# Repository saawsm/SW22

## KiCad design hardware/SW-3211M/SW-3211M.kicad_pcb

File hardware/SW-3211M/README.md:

# SW-3211M, a MK-312 style driver on a stick!

## About
This board aims to bring the hardware of e-stim/EMS/TENS to an easy-to-use module. Think: Sparkfun, Adafruit, etc.

This device tries to mimic the output stage of the well-known Erostec ET312 or better, the DIY reverse engineered MK-312.
Hopefully by recreating this output stage, the same e-stim experience can be achieved as those devices.

Its been designed with the ESP-32 microcontroller in mind (hence SW-32), but should work with others. 

The original design of this module was based on the design by [WendyTeslaburger/WT-312](https://github.com/WendyTeslaburger/WT-312).

## Status
- [x] Create v1.0 Schematic
- [x] Route v1.0 PCB
- [x] Order v1.0 PCBs
- [ ] Review process
- [ ] Add alternative BOM sources

## Gerber & Bill of Materials (BOM)
The Gerber zip file was generated with JLCPCB in mind (excluding assembly).
Two BOM sources are available, the interactive HTML BOM located in `/bom` folder, or on [OctoPart](https://octopart.com/bom-tool/mcb9Iqj6).

## Theory of operation
### Output stage:

Just like the ET/MT312 this stick uses a 42TL004 audio transformer with the primary connected to the TENS output and the secondary connected to some circuitry to generate pulses.

These pulses are generated by the microcontroller, it can control frequency (how many pulses per second) and the duration of each pulse.

A single "pulse"  consists of two steps:
1. Apply a voltage on `PULSE_A`. This will make one of both N-FETs conductive and current will start to flow through half the windings of the transformer.
2. Apply a voltage on `PULSE_B`. This will make current flow through the other half of the transformer and reverse the polarity of the output TENS signal. Thus making this a bi-polar TENS driver.

To prevent the an excessive high drain-source voltage on the N-MOS drivers because of back-EMF generated by the transformer, two diodes will clamp this voltage to a zener diode on top of the centre-tap voltage.

### Level/current control

The intensity of a TENS stimulus is not only defined by the duration and frequency of the pulses, but also by the output power of that pulse. To control the output power of a pulse, we can limit how much current is flowing into the primary side of the transformer.

By controlling the gate-voltage of a P-FET it is possible to control how much current that P-FET will allow to flow. An opamp is used to boost the I/O-voltage of the microcontroller to the 9V needed on the P-FET gate.

Important to note is that the `I_LIMIT` signal is inverted, a 0V means the P-FET is allowing maximal current and a >3.3V will mean the P-FET is turned off.

### Current feedback

Because not all P-FETs are created 100% equally, it is important to first characterize the feedback curve between the `I_LIMIT` signal and the current flowing through the transformer. This curve can be measured by the MCU on a embedded or external ADC on the `I_SENSE` pin of the SW-3211M module.

To keep the voltage lost over the shunt resistor to a minimum, a small value shunt resistor is used and then amplified to the full-range of the ADC by an opamp.

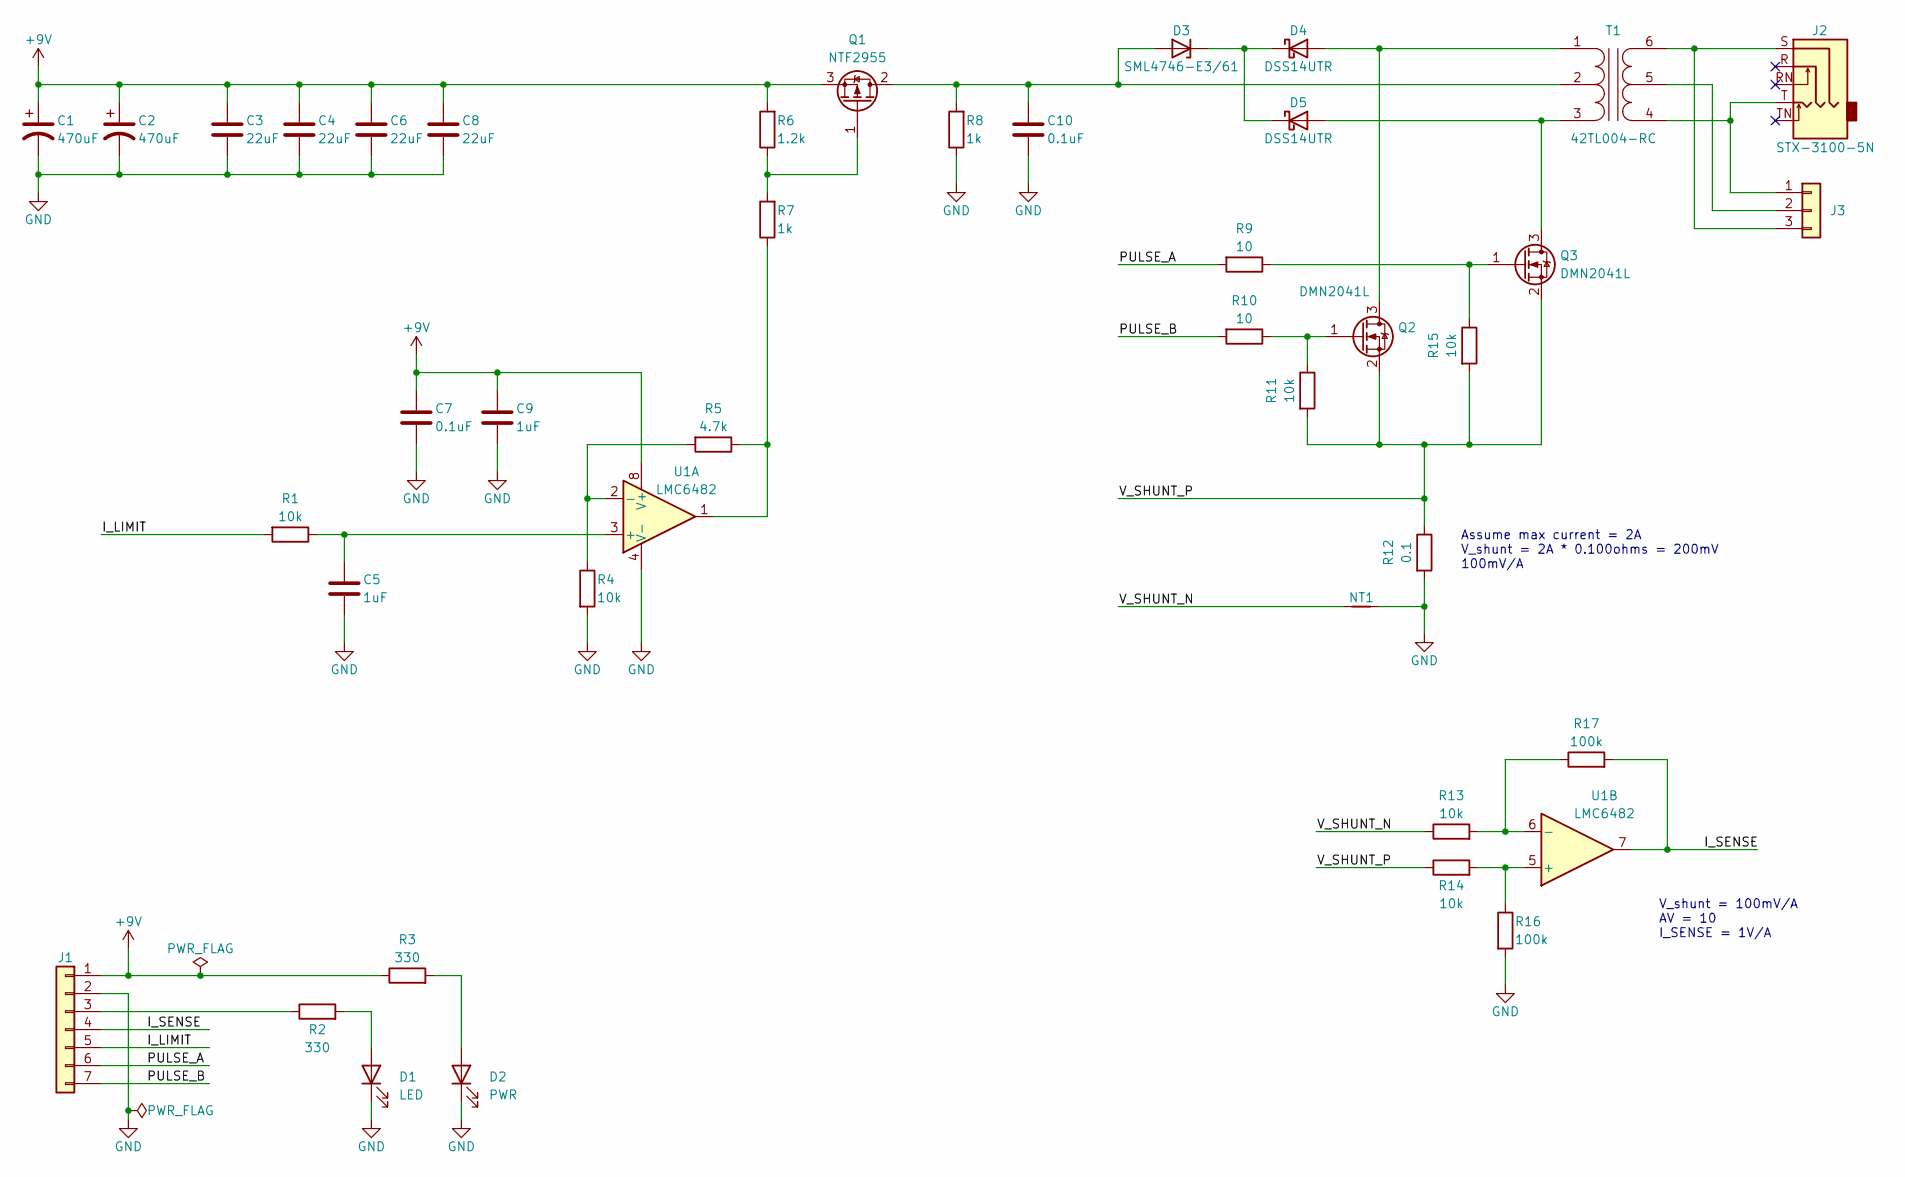
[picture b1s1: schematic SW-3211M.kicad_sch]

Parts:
C1, C2: 470uF; CP_Radial_D8.0mm_P3.50mm; MPN 477CKE016M
C3, C4, C6, C8: 22uF; C_1210_3225Metric; MPN CL32A226MAJNNNE
C5, C9: 1uF; C_0603_1608Metric; MPN CL10B105KA8NNNC
C7, C10: 0.1uF; C_0603_1608Metric; MPN CL10B104KB8WPND
D1: LED; LED_0805_2012Metric
D2: PWR; LED_0805_2012Metric
D3: SML4746-E3/61; D_SMA; MPN SML4746-E3/61
D4, D5: DSS14UTR; D_SOD-123F; MPN DSS14UTR
J1: Conn_01x07; PinHeader_1x07_P2.54mm_Vertical
J2: STX-3100-5N; MPN STX-3100-5N
J3: Conn_01x03; PinHeader_1x03_P2.54mm_Vertical
NT1: NetTie_2; NetTie-2_SMD_Pad0.5mm
Q1: NTF2955; SOT-223-3_TabPin2; MPN NTF2955T1G
Q2, Q3: DMN2041L; SOT-23; MPN DMN2041L-7
R1, R4, R11, R13, R14, R15: 10k; R_0603_1608Metric; MPN AC0603FR-1010KL
R2, R3: 330; R_0603_1608Metric
R5: 4.7k; R_0603_1608Metric; MPN AC0603FR-134K7L
R6: 1.2k; R_0603_1608Metric; MPN AC0603FR-071K2L
R7, R8: 1k; R_0603_1608Metric; MPN AC0603FR-101KL
R9, R10: 10; R_0603_1608Metric; MPN RC0603FR-0710RL
R12: 0.1; R_1206_3216Metric; MPN SCRR1206S1-R100F
R16, R17: 100k; R_0603_1608Metric; MPN CRCW0603100KFKEAC
T1: 42TL004-RC; 42TL; MPN 42TL004-RC
U1: LMC6482; SOIC-8_3.9x4.9mm_P1.27mm; MPN LMC6482IDT

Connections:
+9V: C1.1, C2.1, C3.1, C4.1, C6.1, C7.1, C8.1, C9.1, J1.1, Q1.3 (S), R3.1, R6.2, U1.8 (V+)
/I_LIMIT: J1.5, R1.2
/I_SENSE: J1.4, R17.2, U1.7
/PULSE_A: J1.6, R9.2
/PULSE_B: J1.7, R10.2
/V_SHUNT_N: NT1.1, R13.1
/V_SHUNT_P: Q2.2 (S), Q3.2 (S), R11.2, R12.1, R14.1, R15.2
GND: C1.2, C2.2, C3.2, C4.2, C5.2, C6.2, C7.2, C8.2, C9.2, C10.2, D1.1 (K), D2.1 (K), J1.2, NT1.2, R4.2, R8.1, R12.2, R16.2, U1.4 (V-)
unnamed: C5.1, R1.1, U1.3 (+)
unnamed: C10.1, D3.2 (A), Q1.2 (D), R8.2, T1.2 (PM)
unnamed: D1.2 (A), R2.2
unnamed: D2.2 (A), R3.2
unnamed: D3.1 (K), D4.1 (K), D5.1 (K)
unnamed: D4.2 (A), Q2.3 (D), T1.1 (PR1)
unnamed: D5.2 (A), Q3.3 (D), T1.3 (PR2)
unnamed: J1.3, R2.1
unnamed: J2.S, J3.3, T1.6 (S2)
unnamed: J2.T, J3.1, T1.4 (S1)
unnamed: J3.2, T1.5 (SM)
unnamed: Q1.1 (G), R6.1, R7.2
unnamed: Q2.1 (G), R10.1, R11.1
unnamed: Q3.1 (G), R9.1, R15.1
unnamed: R4.1, R5.2, U1.2 (-)
unnamed: R5.1, R7.1, U1.1
unnamed: R13.2, R17.1, U1.6 (-)
unnamed: R14.2, R16.1, U1.5 (+)

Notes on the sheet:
Assume max current = 2A V_shunt = 2A * 0.100ohms = 200mV 100mV/A
V_shunt = 100mV/A AV = 10 I_SENSE = 1V/A

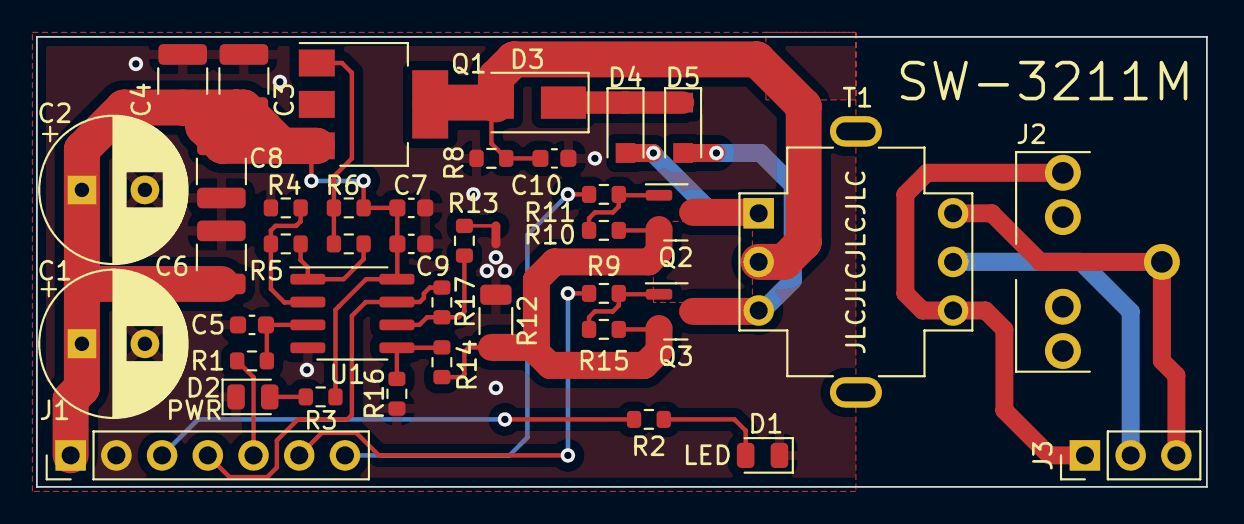
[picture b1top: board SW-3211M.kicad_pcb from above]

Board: 2 copper layers, 65.0 x 25.0 mm, 41 parts (0 on the bottom side), 26 nets.

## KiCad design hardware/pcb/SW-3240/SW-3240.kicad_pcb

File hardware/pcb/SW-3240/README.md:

# SW-3240 - Main Board

## About
This is a main board of SW-32. This specific board supports up to 4 output channels.
It provides power (+3.3V, +5V, and +9V), battery charging, and low-level control of the output modules.

## Status
- [x] Create v1.0 Schematic
- [x] Route v1.0 PCB
- [ ] Order v1.0 PCBs
- [ ] Review 

## Gerber & Bill of Materials (BOM)
The Gerber zip file was generated with JLCPCB in mind (excluding assembly).
Two BOM sources are available, the interactive HTML BOM located in `/bom` folder.

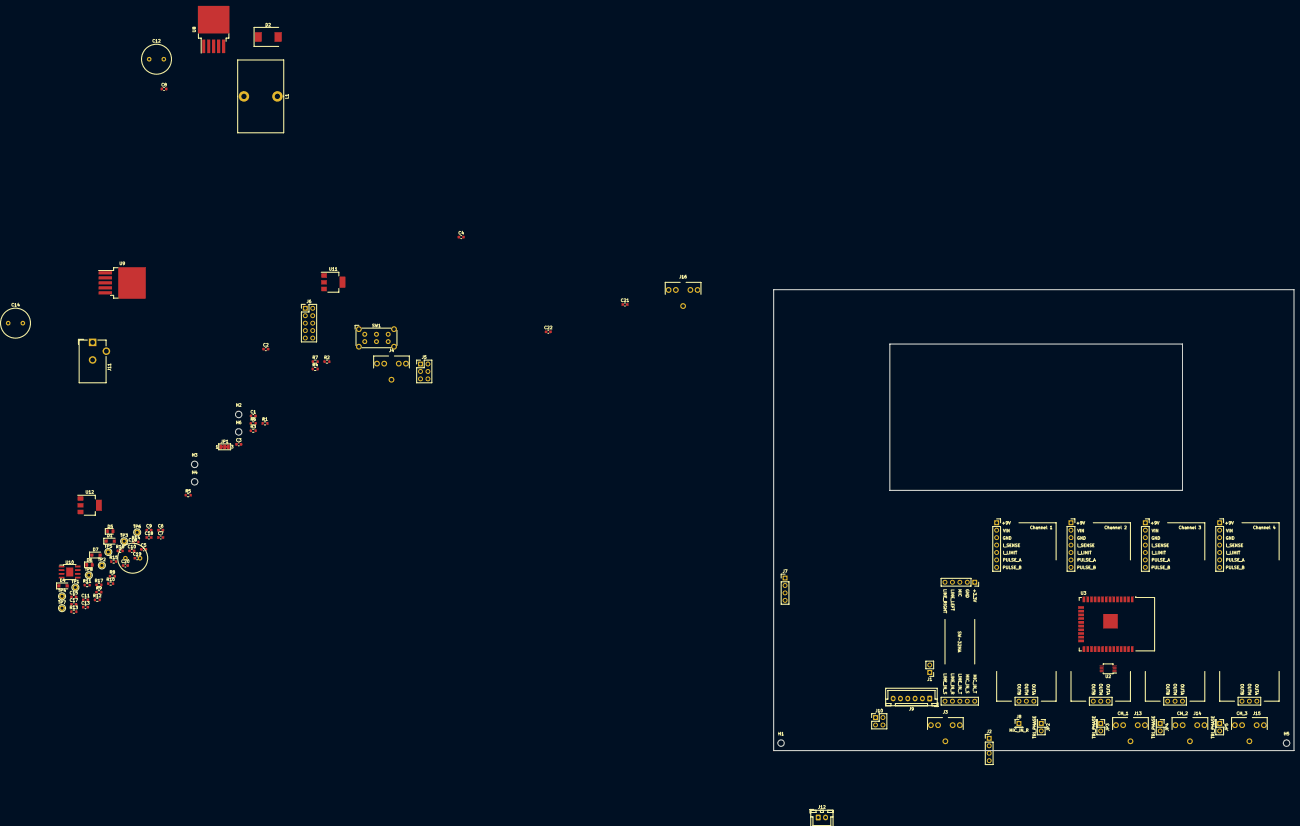
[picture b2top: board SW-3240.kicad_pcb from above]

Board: 2 copper layers, 177.8 x 157.5 mm, 94 parts (0 on the bottom side), 80 nets, no tracks yet.

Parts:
C1, C5, C7, C15, C17, C18, C19, C20: 10uF; C_0603_1608Metric
C2, C6, C13, C21, C22: 100nF; C_0603_1608Metric
C3, C8, C9: 100uF; C_0603_1608Metric
C4: 1uF; C_0603_1608Metric
C10: 470nF; C_0603_1608Metric
C11: 22nF; C_0603_1608Metric
C12, C14, C16: 1000uF; C_Radial_D10.0mm_H20.0mm_P5.00mm
D1, D4, D7: 1N4004; D_SOD-123F
D2: SS34; D_SMC
D5, D6: RED; LED_0805_2012Metric
H1, H2, H3, H4, H5, H6: MountingHole; MountingHole_2.2mm_M2
J1: AUX_MIC_IN; PinHeader_1x02_P2.54mm_Vertical
J2: AUX_LINE_IN; PinHeader_1x04_P2.54mm_Vertical
J3: MIC; STX-3100-5N
J4: LINE IN; STX-3100-5N
J5: ESPFlash; PinHeader_2x03_P2.54mm_Vertical
J6: JTAG; PinHeader_2x05_P2.54mm_Vertical
J7: I2C; PinHeader_1x04_P2.54mm_Vertical
J8: MIC_IN_R; PinHeader_1x01_P2.54mm_Vertical
J9: FP_IO; JST_XH_B6B-XH-A_1x06_P2.50mm_Vertical
J10: RESET/FLASH; PinHeader_2x02_P2.54mm_Vertical
J11: PWR; BarrelJack_CUI_PJ-102AH_Horizontal
J12: BAT; JST_XH_B2B-XH-A_1x02_P2.50mm_Vertical
J13: CH_1; STX-3100-5N
J14: CH_2; STX-3100-5N
J15: CH_3; STX-3100-5N
J16: CH_4; STX-3100-5N
JP1: SolderJumper_3_Bridged123; SolderJumper-3_P1.3mm_Bridged123_Pad1.0x1.5mm_NumberLabels
JP2, JP3, JP4, JP5: TRI_PHASE; PinHeader_2x01_P2.54mm_Vertical
L1: 100uH; L_Toroid_Vertical_L24.6mm_W15.5mm_P11.44mm_Pulse_KM-4
R1, R2, R6, R7, R17: 2.7K; R_0603_1608Metric
R3, R10, R16: 10K; R_0603_1608Metric
R4, R5: 10k; R_0603_1608Metric
R8, R12: 100K; R_0603_1608Metric
R9: 84.5K; R_0603_1608Metric
R11, R14: 1K; R_0603_1608Metric
R13: 9K; R_0603_1608Metric
R15: 470; R_0603_1608Metric
SW1: PWR_SW; SW_E-Switch_EG2219_DPDT_Angled
TP1: EN; TestPoint_THTPad_D2.0mm_Drill1.0mm
TP2: 5V; TestPoint_THTPad_D2.0mm_Drill1.0mm
TP3: 14V; TestPoint_THTPad_D2.0mm_Drill1.0mm
TP4: 9V; TestPoint_THTPad_D2.0mm_Drill1.0mm
TP5: 13.5V; TestPoint_THTPad_D2.0mm_Drill1.0mm
TP6: 12V; TestPoint_THTPad_D2.0mm_Drill1.0mm
TP7: 3.3V; TestPoint_THTPad_D2.0mm_Drill1.0mm
TP8: 3.3V_ALT; TestPoint_THTPad_D2.0mm_Drill1.0mm
U1: SW-32MA; SW-32MA_Socket
U2: MCP4728; MSOP-10_3x3mm_P0.5mm
U3: ESP32-WROOM-32D; ESP32-WROOM-32
U4: Channel 1; SW-32MO_Socket
U5: Channel 2; SW-32MO_Socket
U6: Channel 3; SW-32MO_Socket
U7: Channel 4; SW-32MO_Socket
U8: LM2576-5; TO-263-5_TabPin3
U9: LM2941; TO-263-5_TabPin3
U10: LMR14050; TI_SO-PowerPAD-8
U11, U12: NCP1117-3.3; SOT-223-3_TabPin2

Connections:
+3V3: C1.1, C2.1, C3.1, C5.1, C6.1, C19.1, C21.1, J5.2, J6.1, J7.2, JP1.2 (C), R1.1, R2.1, R4.2, R5.2, R15.2, TP7.1, U1.1 (+3.3V), U2.1 (VDD), U3.2 (VDD), U4.2 (VIN), U5.2 (VIN), U6.2 (VIN), U7.2 (VIN), U11.2 (VO)
+5V: C12.1, C15.1, C17.1, C18.1, L1.2, TP2.1, U8.4 (FB), U11.3 (VI), U12.3 (VI)
+9V: R12.1, R14.2, TP4.1, U4.1 (+9V), U5.1 (+9V), U6.1 (+9V), U7.1 (+9V)
+12V: C7.1, C8.1, C9.1, R16.1, SW1.2 (B), TP6.1, U8.1 (VIN), U10.2 (VIN)
/+3.3V_FP: C20.1, C22.1, J9.2, TP8.1, U12.2 (VO)
/CHA_I_LIMIT: U2.6 (VOUTA), U4.5 (I_LIMIT)
/CHA_I_SENSE: U3.7 (IO35), U4.4 (I_SENSE)
/CHA_PULSE_A: U3.26 (IO4), U4.6 (PULSE_A)
/CHA_PULSE_B: U3.24 (IO2), U4.7 (PULSE_B)
/CHB_I_LIMIT: U2.7 (VOUTB), U5.5 (I_LIMIT)
/CHB_I_SENSE: U3.6 (IO34), U5.4 (I_SENSE)
/CHB_PULSE_A: U3.31 (IO19), U5.6 (PULSE_A)
/CHB_PULSE_B: U3.30 (IO18), U5.7 (PULSE_B)
/CHC_I_LIMIT: U2.8 (VOUTC), U6.5 (I_LIMIT)
/CHC_I_SENSE: U3.5 (SENSOR_VN), U6.4 (I_SENSE)
/CHC_PULSE_A: U3.37 (IO23), U6.6 (PULSE_A)
/CHC_PULSE_B: U3.9 (IO33), U6.7 (PULSE_B)
/CHD_I_LIMIT: U2.9 (VOUTD), U7.5 (I_LIMIT)
/CHD_I_SENSE: U3.4 (SENSOR_VP), U7.4 (I_SENSE)
/CHD_PULSE_A: U3.28 (IO17), U7.6 (PULSE_A)
/CHD_PULSE_B: U3.27 (IO16), U7.7 (PULSE_B)
/CH_PSU_EN: J9.5, R8.1, TP1.1, U10.3 (EN)
/DAC_SCL: R1.2, U2.2 (SCL), U3.29 (IO5)
/DAC_SDA: R2.2, U2.3 (SDA), U3.8 (IO32)
/EN: C4.1, J5.1, J10.2, R5.1, U3.3 (EN)
/IO0: J5.6, J10.4, R4.1, U3.25 (IO0)
/LINE_LEFT: U1.4 (LINE_LEFT), U3.11 (IO26)
/LINE_RIGHT: U1.5 (LINE_RIGHT), U3.10 (IO25)
/MIC: U1.3 (MIC), U3.12 (IO27)
/MTCK: J6.4, U3.16 (IO13)
/MTDI: J6.8, U3.14 (IO12)
/MTDO: J6.6, U3.23 (IO15)
/MTMS: J6.2, U3.13 (IO14)
/PSU/VIN: D1.2 (A), J11.1
/RXD: J5.5, U3.34 (RXD0/IO3)
/SCL: J7.3, J9.3, R6.2, U3.36 (IO22)
/SDA: J7.4, J9.4, R7.2, U3.33 (IO21)
/TXD: J5.3, U3.35 (TXD0/IO1)
/VBAT_SENSE: J9.6, R16.2, R17.1
GND: C1.2, C2.2, C3.2, C4.2, C5.2, C6.2, C7.2, C8.2, C9.2, C10.2, C11.1, C12.2, C14.2, C15.2, C16.2, C17.2, C18.2, C19.2, C20.2, C21.2, C22.2, D2.2 (A), D5.1 (K), D6.1 (K), D7.2 (A), J5.4, J6.3, J7.1, J9.1, J10.1, J10.3, J11.2, J12.2, R3.1, R8.2, R9.2, R11.2, R13.2, R17.2, U1.2 (GND), U2.10 (VSS), U3.1 (GND), U3.15 (GND), U3.38 (GND), U3.39 (GND), U4.3 (GND), U5.3 (GND), U6.3 (GND), U7.3 (GND), U8.3 (GND), U8.5 (~ON/OFF), U9.2 (ON/OFF), U9.3 (GND), U10.7 (GND), U10.9 (GNDPAD), U11.1 (GND), U12.1 (GND)
unnamed: C10.1, D1.1 (K), U9.4 (IN)
unnamed: C11.2, U10.6 (SS)
unnamed: C13.1, U10.1 (BOOT)
unnamed: C13.2, U10.8 (SW)
unnamed: C14.1, D4.2 (A), R10.1, TP3.1, U9.5 (OUT)
unnamed: C16.1, D7.1 (K), SW1.1 (A), TP5.1
unnamed: D2.1 (K), L1.1, U8.2 (OUT)
unnamed: D5.2 (A), R14.1
unnamed: D6.2 (A), R15.1
unnamed: J1.1, J3.S, U1.7 (MIC_IN_S)
unnamed: J1.2, J3.TN
unnamed: J2.1, J4.TN
unnamed: J2.2, J2.3, J4.S, U1.10 (LINE_IN_S)
unnamed: J2.4, J4.RN
unnamed: J3.R, J8.1
unnamed: J3.T, U1.6 (MIC_IN_T)
unnamed: J4.R, U1.9 (LINE_IN_R)
unnamed: J4.T, U1.8 (LINE_IN_T)
unnamed: J13.R, JP2.2 (B)
unnamed: J13.S, U4.8 (OUTA)
unnamed: J13.T, U4.10 (OUTB)
unnamed: J14.R, JP3.2 (B)
unnamed: J14.S, U5.8 (OUTA)
unnamed: J14.T, U5.10 (OUTB)
unnamed: J15.R, JP4.2 (B)
unnamed: J15.S, U6.8 (OUTA)
unnamed: J15.T, U6.10 (OUTB)
unnamed: J16.R, JP5.2 (B)
unnamed: J16.S, U7.8 (OUTA)
unnamed: J16.T, U7.10 (OUTB)
unnamed: JP1.1 (A), R7.1
unnamed: JP1.3 (B), R6.1
unnamed: JP2.1 (A), U4.9 (OUTM)
unnamed: JP3.1 (A), U5.9 (OUTM)
unnamed: JP4.1 (A), U6.9 (OUTM)
unnamed: JP5.1 (A), U7.9 (OUTM)
unnamed: R3.2, U2.4 (~LDAC)
unnamed: R9.1, U10.4 (RT/SYNC)
unnamed: R10.2, R11.1, U9.1 (ADJ)
unnamed: R12.2, R13.1, U10.5 (FB)

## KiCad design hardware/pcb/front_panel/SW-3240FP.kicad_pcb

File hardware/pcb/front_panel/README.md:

# SW-324FP - Front Panel

## About
This is the front panel board for the SW-324. It connects via the I2C expansion connector on the main board.

## Status
- [x] Create v1.1 Schematic
- [ ] Route v1.1 PCB
- [ ] Order v1.1 PCBs
- [ ] Review

## Gerber & Bill of Materials (BOM)
The Gerber zip file was generated with [JLCPCB](https://jlcpcb.com/) in mind (excluding assembly).
Two BOM sources are available, the interactive HTML BOM located in `/bom` folder, and a CSV file.

### Excluded BOM Items:
- 0.1" break-away pin headers/sockets
- Misc connectors

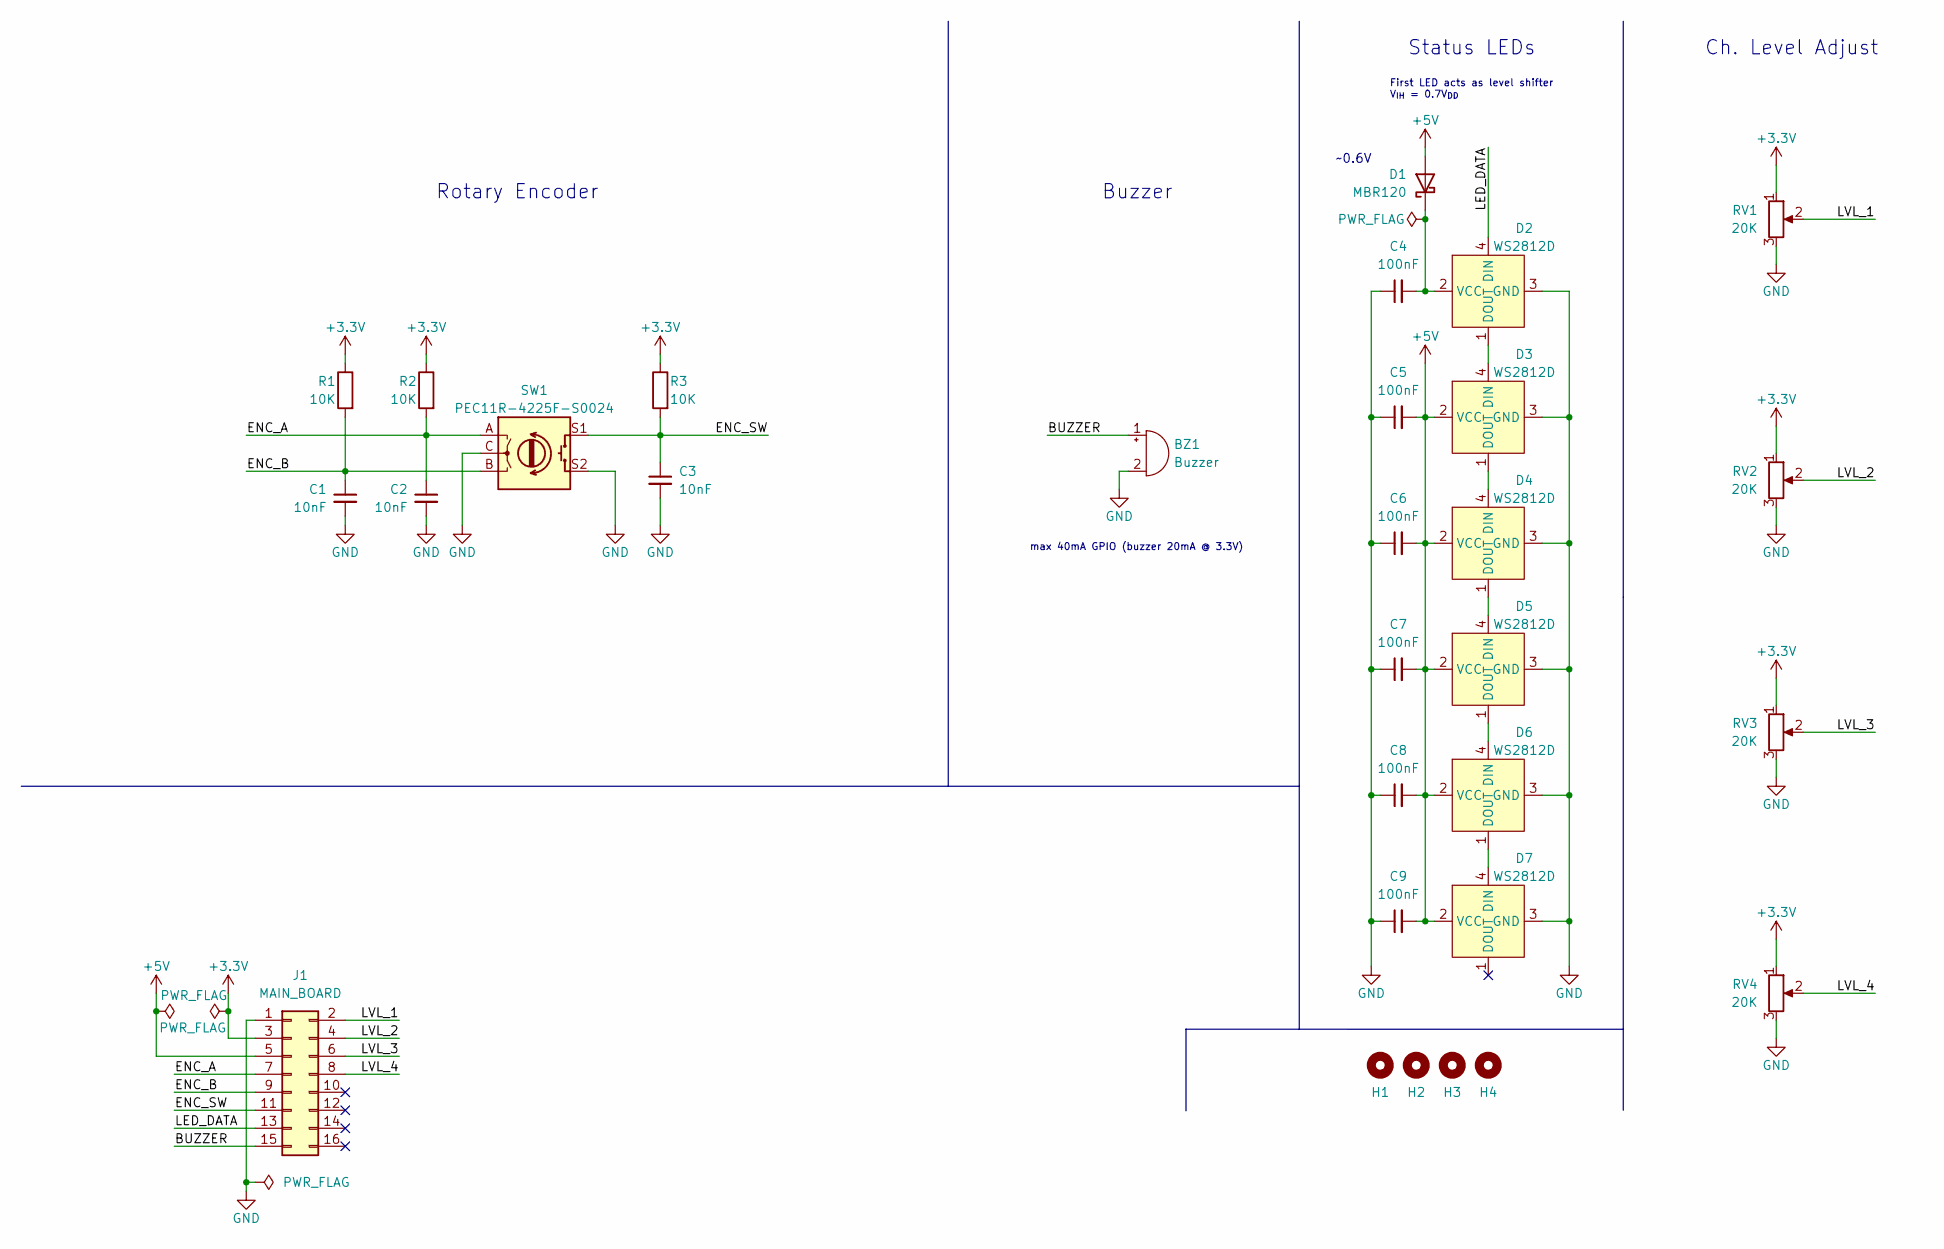
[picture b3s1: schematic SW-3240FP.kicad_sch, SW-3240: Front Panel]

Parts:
BZ1: Buzzer; Buzzer_12x9.5RM7.6; MPN IE122303-1; MOUSER 497-IE122303-1
C1, C2, C3: 10nF; C_0603_1608Metric; MPN CL10B103KB8NNNC; LCSC C1589
C4, C5, C6, C7, C8, C9: 100nF; C_0603_1608Metric; MPN CL10B104KB8NNNC; LCSC C1591
D1: MBR120; D_SOD-123F; MPN MBR120ESFT1G; MOUSER 863-MBR120ESFT1G
D2, D3, D4, D5, D6, D7: WS2812D; WS2812D-F5; MPN WS2812D-F5; LCSC C190565
H1, H2, H3, H4: MountingHole; MountingHole_2.2mm_M2
J1: MAIN_BOARD; PinHeader_2x08_P2.54mm_Vertical
R1, R2, R3: 10K; R_0603_1608Metric; MPN RC0603FR-0710KL; LCSC C98220
RV1, RV2, RV3, RV4: 20K; Potentiometer_Bourns_PTV09A-1_Single_Vertical; MPN PTV09A-40xxS-A203
SW1: PEC11R-4225F-S0024; Rotary_Encoder_Switched_PEC11R; MPN PEC11R-42xxK-S0024

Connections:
+3V3: J1.3, R1.1, R2.1, R3.1, RV1.1, RV2.1, RV3.1, RV4.1
+5V: C5.2, C6.2, C7.2, C8.2, C9.2, D1.2 (A), D3.2 (VCC), D4.2 (VCC), D5.2 (VCC), D6.2 (VCC), D7.2 (VCC), J1.5
/BUZZER: BZ1.1 (-), J1.15
/ENC_A: C2.1, J1.7, R2.2, SW1.A
/ENC_B: C1.1, J1.9, R1.2, SW1.B
/ENC_SW: C3.1, J1.11, R3.2, SW1.S1
/LED_DATA: D2.4 (DIN), J1.13
/LVL_1: J1.2, RV1.2
/LVL_2: J1.4, RV2.2
/LVL_3: J1.6, RV3.2
/LVL_4: J1.8, RV4.2
GND: BZ1.2 (+), C1.2, C2.2, C3.2, C4.1, C5.1, C6.1, C7.1, C8.1, C9.1, D2.3 (GND), D3.3 (GND), D4.3 (GND), D5.3 (GND), D6.3 (GND), D7.3 (GND), J1.1, RV1.3, RV2.3, RV3.3, RV4.3, SW1.C, SW1.S2
unnamed: C4.2, D1.1 (K), D2.2 (VCC)
unnamed: D2.1 (DOUT), D3.4 (DIN)
unnamed: D3.1 (DOUT), D4.4 (DIN)
unnamed: D4.1 (DOUT), D5.4 (DIN)
unnamed: D5.1 (DOUT), D6.4 (DIN)
unnamed: D6.1 (DOUT), D7.4 (DIN)

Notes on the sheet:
Status LEDs
~0.6V
Rotary Encoder
Ch. Level Adjust
Buzzer
First LED acts as level shifter V_{IH} = 0.7V_{DD}
max 40mA GPIO (buzzer 20mA @ 3.3V)

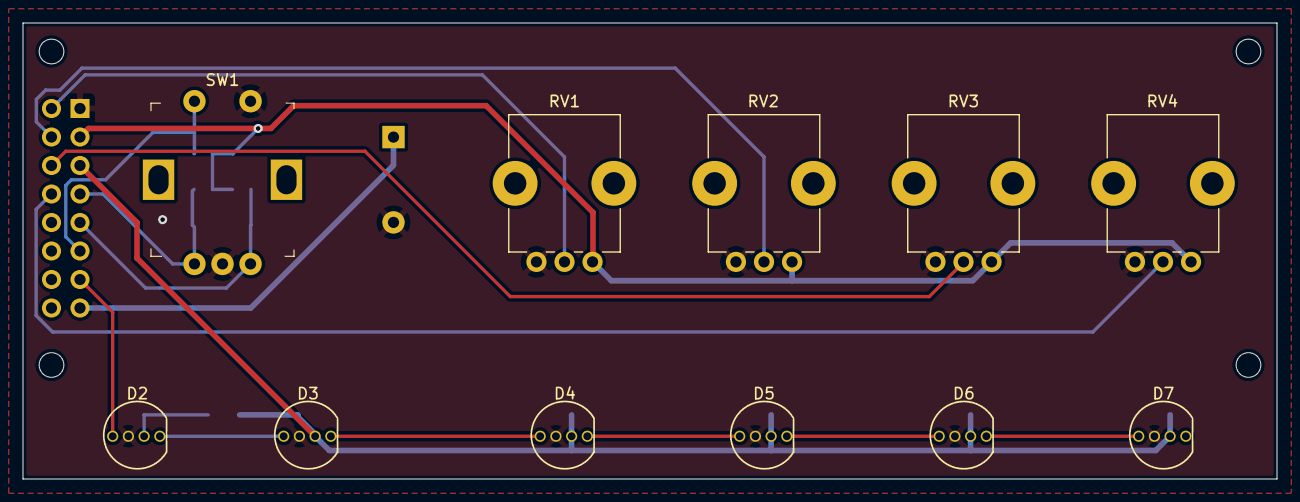
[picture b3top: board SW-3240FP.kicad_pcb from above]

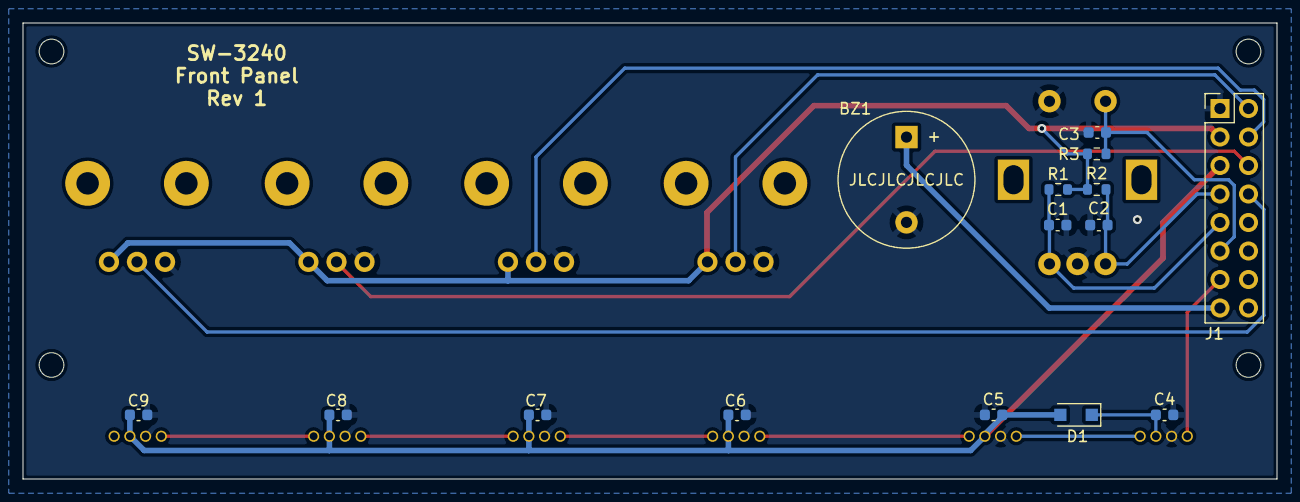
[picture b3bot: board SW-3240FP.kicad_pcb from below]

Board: 2 copper layers, 111.8 x 40.6 mm, 30 parts (19 on the bottom side), 18 nets.

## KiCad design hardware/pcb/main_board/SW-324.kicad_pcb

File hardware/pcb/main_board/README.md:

# SW-324 - Main Board

## About
This is a main board of SW-324. It supports a max of four output (stim) channels, and two AUX channels.
It provides power (+3.3V, +5V, and +9V), battery charging, low-level control of the output modules (via a Raspberry Pi Pico), and high-level control via an ESP-32.

Each of the four output channels can be potentially repurposed for other uses (since each channel is a module board). Each channel has the following connections controlled by the Raspberry Pi Pico:
- 2x GPIO
- 1x 12-bit ADC
- 1x 12-bit DAC
- +9V 3A max (between all channels)
- +3.3V 1A max (main board total)

## Status
- [x] Create v1.1 Schematic
- [ ] Route v1.1 PCB
- [ ] Order v1.1 PCBs
- [ ] Review

## Gerber & Bill of Materials (BOM)
The Gerber zip file was generated with [JLCPCB](https://jlcpcb.com/) in mind (excluding assembly).
Two BOM sources are available, the interactive HTML BOM located in `/bom` folder, and a CSV file.

### Excluded BOM Items:
- 0.1" break-away pin headers/sockets
- Misc connectors

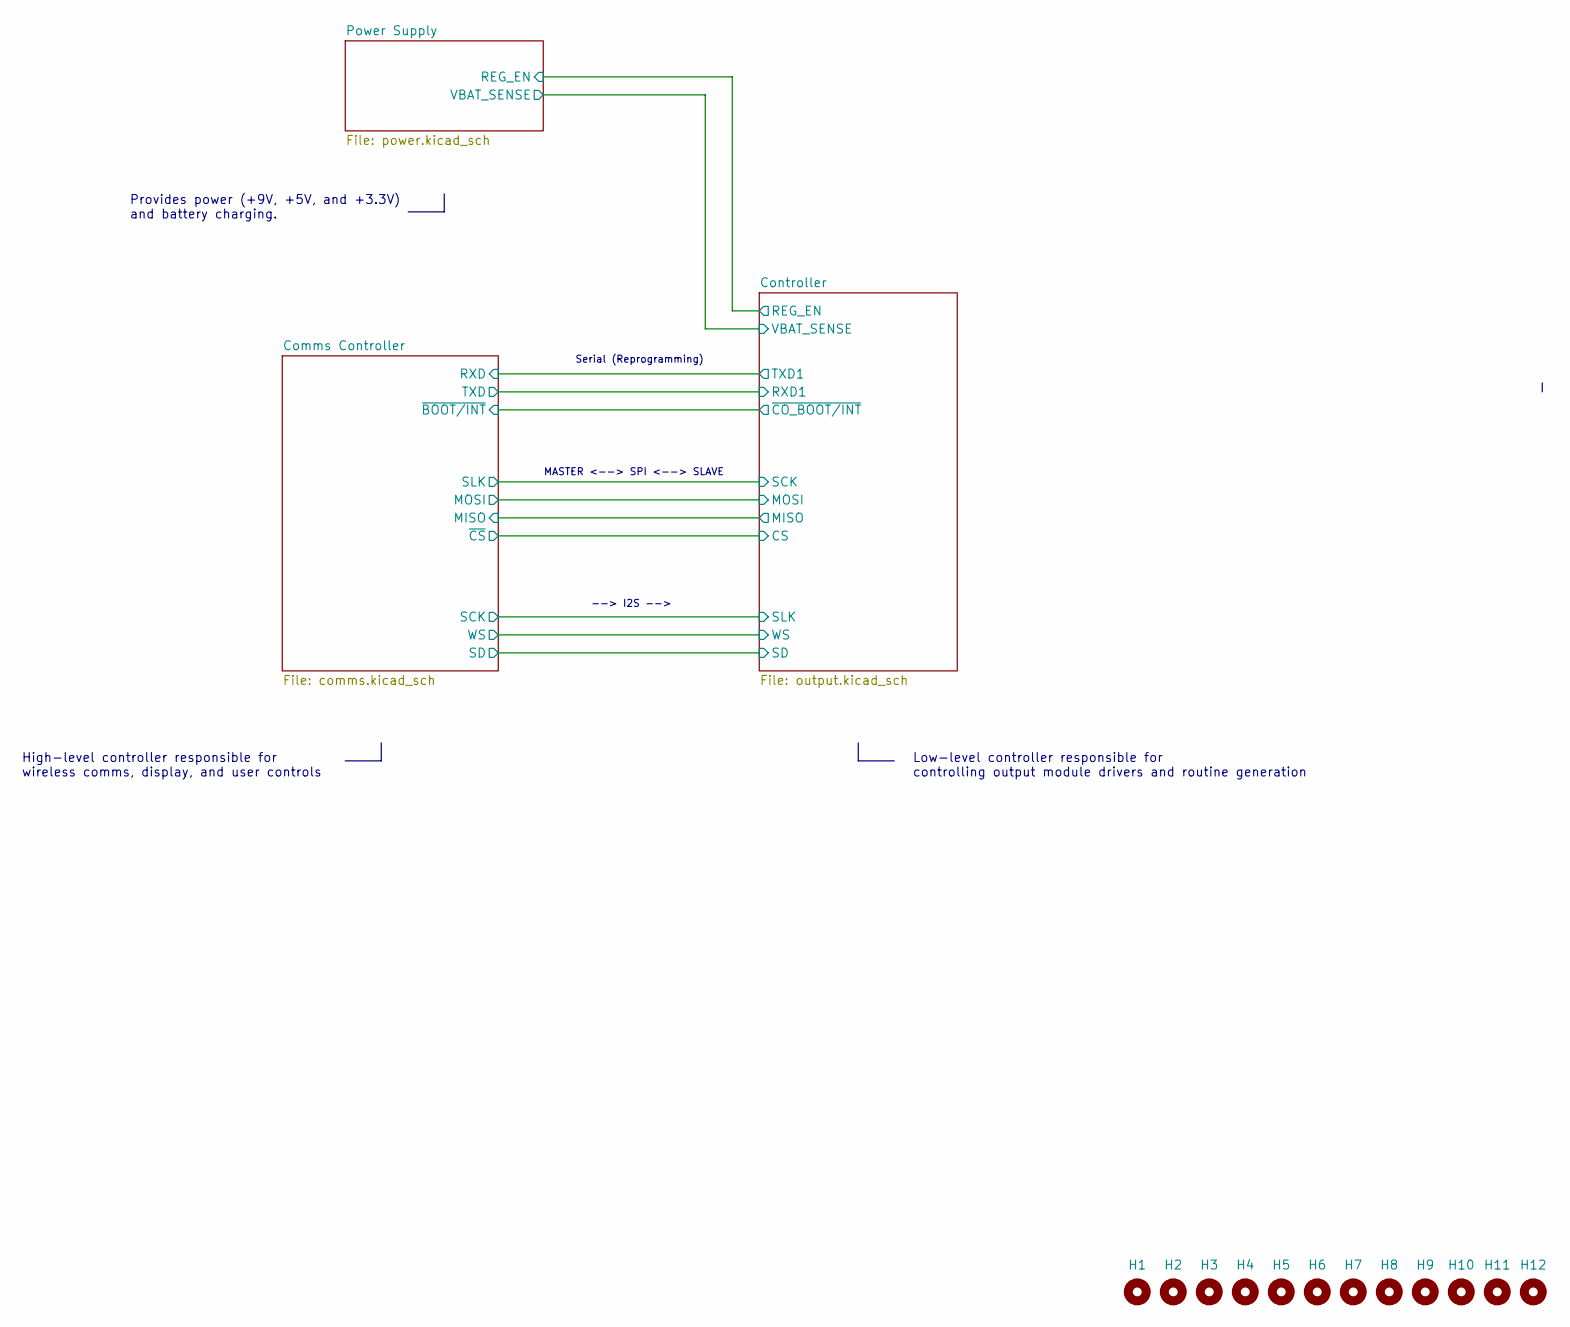
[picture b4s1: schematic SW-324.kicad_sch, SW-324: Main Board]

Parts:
H1, H2, H3, H4, H5, H6, H7, H8, H9, H10, H11, H12: MountingHole; MountingHole_2.2mm_M2

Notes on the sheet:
MASTER <--> SPI <--> SLAVE
--> I2S -->
Low-level controller responsible for controlling output module drivers and routine generation
Provides power (+9V, +5V, and +3.3V) and battery charging.
High-level controller responsible for wireless comms, display, and user controls
Serial (Reprogramming)

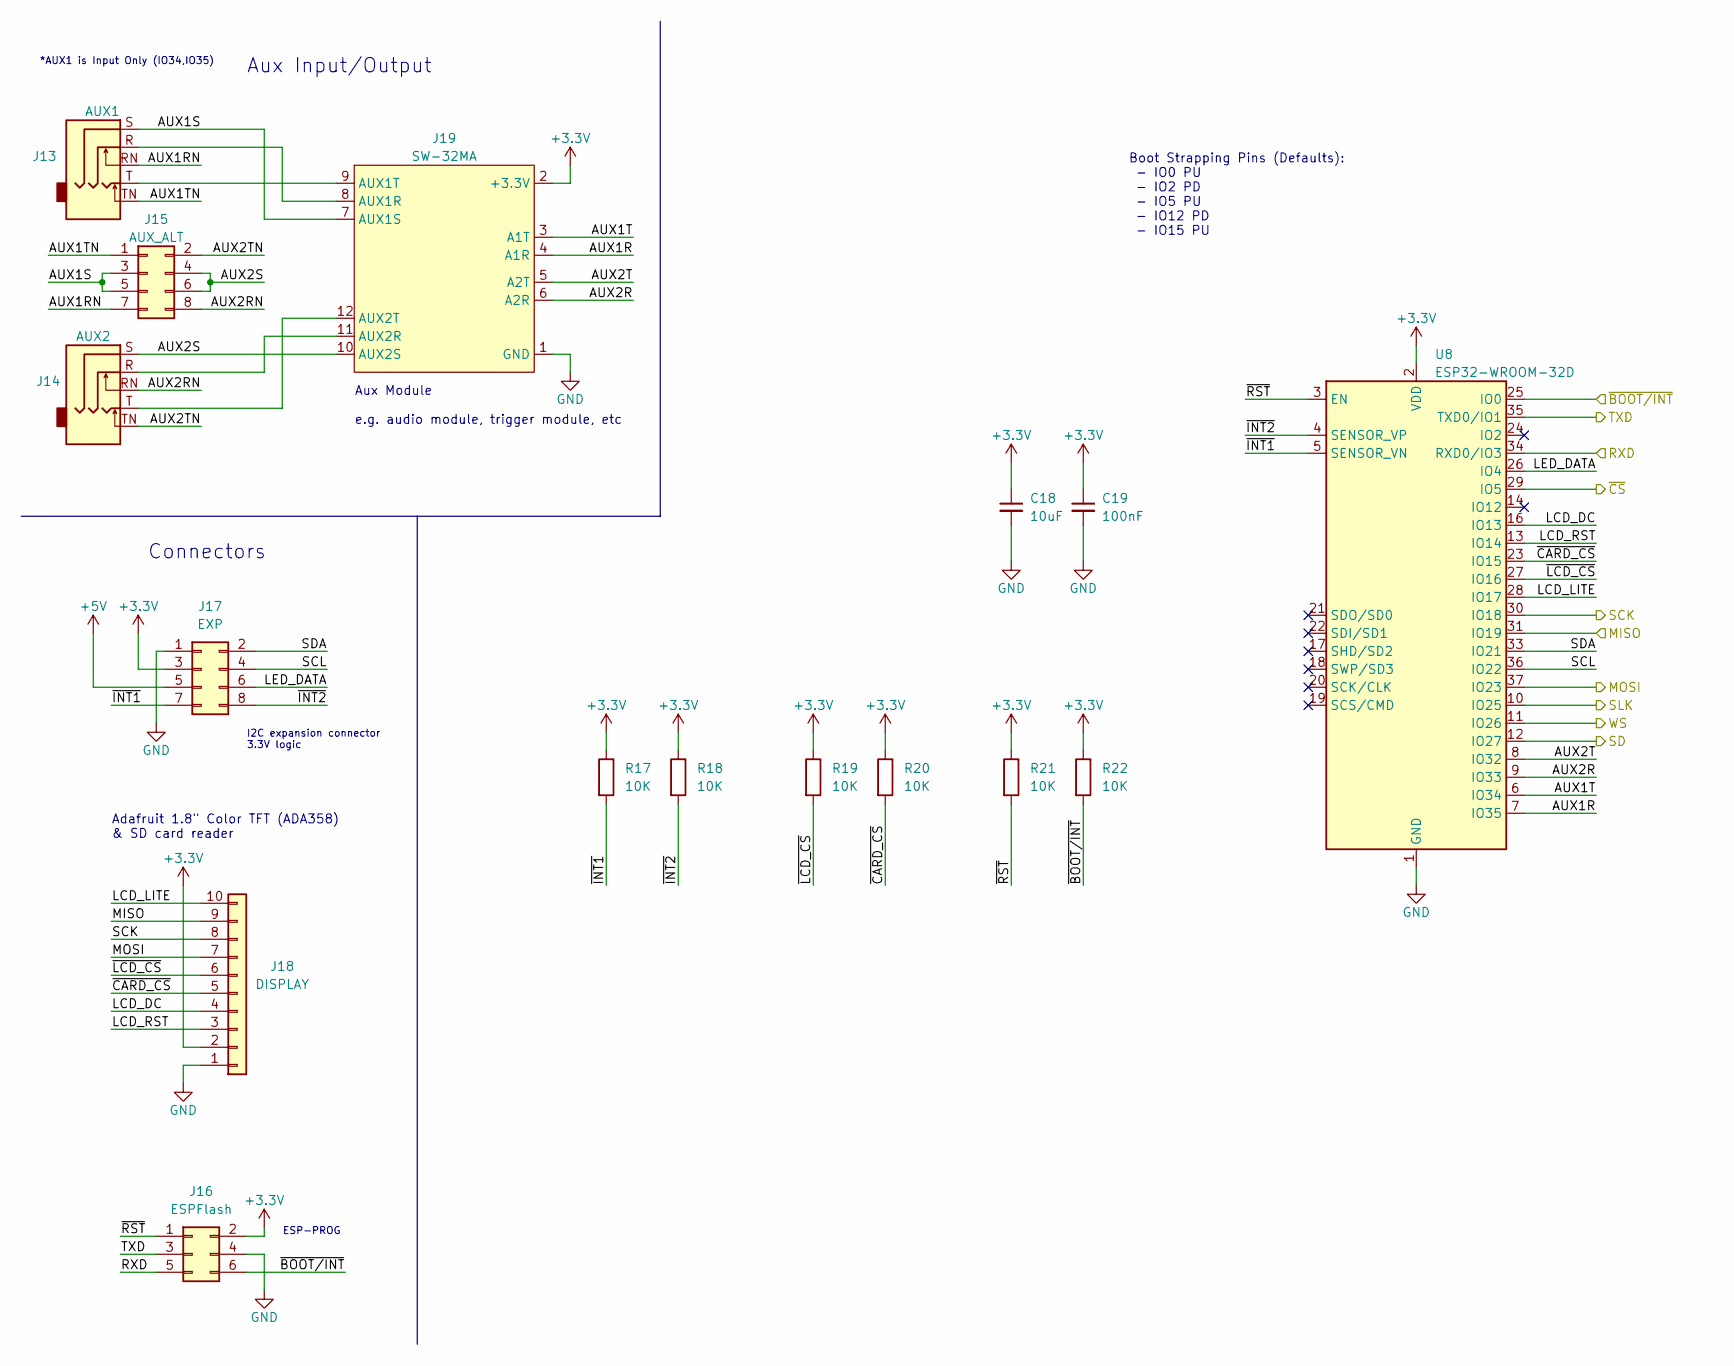
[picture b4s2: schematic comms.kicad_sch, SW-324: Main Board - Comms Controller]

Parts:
C18: 10uF; C_0603_1608Metric; MPN CL10A106MA8NRNC; MOUSER 187-CL10A106MA8NRNC
C19: 100nF; C_0603_1608Metric; MPN CL10B104KB8NNNC; MOUSER 187-CL10B104KB8NNNC
J13: AUX1; STX-3100-5N; MPN STX-3100-5N; MOUSER 806-STX-3100-5N
J14: AUX2; STX-3100-5N; MPN STX-3100-5N; MOUSER 806-STX-3100-5N
J15: AUX_ALT; PinHeader_2x04_P2.54mm_Vertical
J16: ESPFlash; IDC-Header_2x03_P2.54mm_Vertical
J17: EXP; IDC-Header_2x04_P2.54mm_Vertical
J18: DISPLAY; PinHeader_1x10_P2.54mm_Vertical
J19: SW-32MA; SW-32MA_Socket
R17, R18, R19, R20, R21, R22: 10K; R_0603_1608Metric; MPN RC0603FR-0710KL; MOUSER 603-RC0603FR-0710KL
U8: ESP32-WROOM-32D; ESP32-WROOM-32; MPN ESP32-WROOM-32D

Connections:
+3V3: C18.1, C19.1, J16.2, J17.3, J18.2, J19.2 (+3.3V), R17.1, R18.1, R19.1, R20.1, R21.1, R22.1, U8.2 (VDD); also elsewhere on the board
+5V: J17.5; also elsewhere on the board
/Comms Controller/AUX1R: J19.4 (A1R), U8.7 (IO35)
/Comms Controller/AUX1RN: J13.RN, J15.7
/Comms Controller/AUX1S: J13.S, J15.3, J15.5, J19.7 (AUX1S)
/Comms Controller/AUX1T: J19.3 (A1T), U8.6 (IO34)
/Comms Controller/AUX1TN: J13.TN, J15.1
/Comms Controller/AUX2R: J19.6 (A2R), U8.9 (IO33)
/Comms Controller/AUX2RN: J14.RN, J15.8
/Comms Controller/AUX2S: J14.S, J15.4, J15.6, J19.10 (AUX2S)
/Comms Controller/AUX2T: J19.5 (A2T), U8.8 (IO32)
/Comms Controller/AUX2TN: J14.TN, J15.2
/Comms Controller/LCD_DC: J18.4, U8.16 (IO13)
/Comms Controller/LCD_LITE: J18.10, U8.28 (IO17)
/Comms Controller/LCD_RST: J18.3, U8.13 (IO14)
/Comms Controller/LED_DATA: J17.6, U8.26 (IO4)
/Comms Controller/MISO: J18.9, U8.31 (IO19); also elsewhere on the board
/Comms Controller/MOSI: J18.7, U8.37 (IO23); also elsewhere on the board
/Comms Controller/RXD: J16.5, U8.34 (RXD0/IO3); also elsewhere on the board
/Comms Controller/SCK: J18.8, U8.30 (IO18); also elsewhere on the board
/Comms Controller/SCL: J17.4, U8.36 (IO22)
/Comms Controller/SD: U8.12 (IO27); also elsewhere on the board
/Comms Controller/SDA: J17.2, U8.33 (IO21)
/Comms Controller/SLK: U8.10 (IO25); also elsewhere on the board
/Comms Controller/TXD: J16.3, U8.35 (TXD0/IO1); also elsewhere on the board
/Comms Controller/WS: U8.11 (IO26); also elsewhere on the board
/Comms Controller/~BOOT/INT: J16.6, R22.2, U8.25 (IO0); also elsewhere on the board
/Comms Controller/~CARD_CS: J18.5, R20.2, U8.23 (IO15)
/Comms Controller/~CS: U8.29 (IO5); also elsewhere on the board
/Comms Controller/~INT1: J17.7, R17.2, U8.5 (SENSOR_VN)
/Comms Controller/~INT2: J17.8, R18.2, U8.4 (SENSOR_VP)
/Comms Controller/~LCD_CS: J18.6, R19.2, U8.27 (IO16)
/Comms Controller/~RST: J16.1, R21.2, U8.3 (EN)
GND: C18.2, C19.2, J16.4, J17.1, J18.1, J19.1 (GND), U8.1 (GND), U8.15 (GND), U8.38 (GND), U8.39 (GND); also elsewhere on the board
unnamed: J13.R, J19.8 (AUX1R)
unnamed: J13.T, J19.9 (AUX1T)
unnamed: J14.R, J19.11 (AUX2R)
unnamed: J14.T, J19.12 (AUX2T)

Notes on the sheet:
I2C expansion connector 3.3V logic
Adafruit 1.8" Color TFT (ADA358) & SD card reader
ESP-PROG
Aux Module e.g. audio module, trigger module, etc
*AUX1 is Input Only (IO34,IO35)
Aux Input/Output
Connectors
Boot Strapping Pins (Defaults): - IO0 PU - IO2 PD - IO5 PU - IO12 PD - IO15 PU
